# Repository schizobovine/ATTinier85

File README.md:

# ATTinier85
Smallish form factor ATTiny85 platform that doesn't bother with USB.

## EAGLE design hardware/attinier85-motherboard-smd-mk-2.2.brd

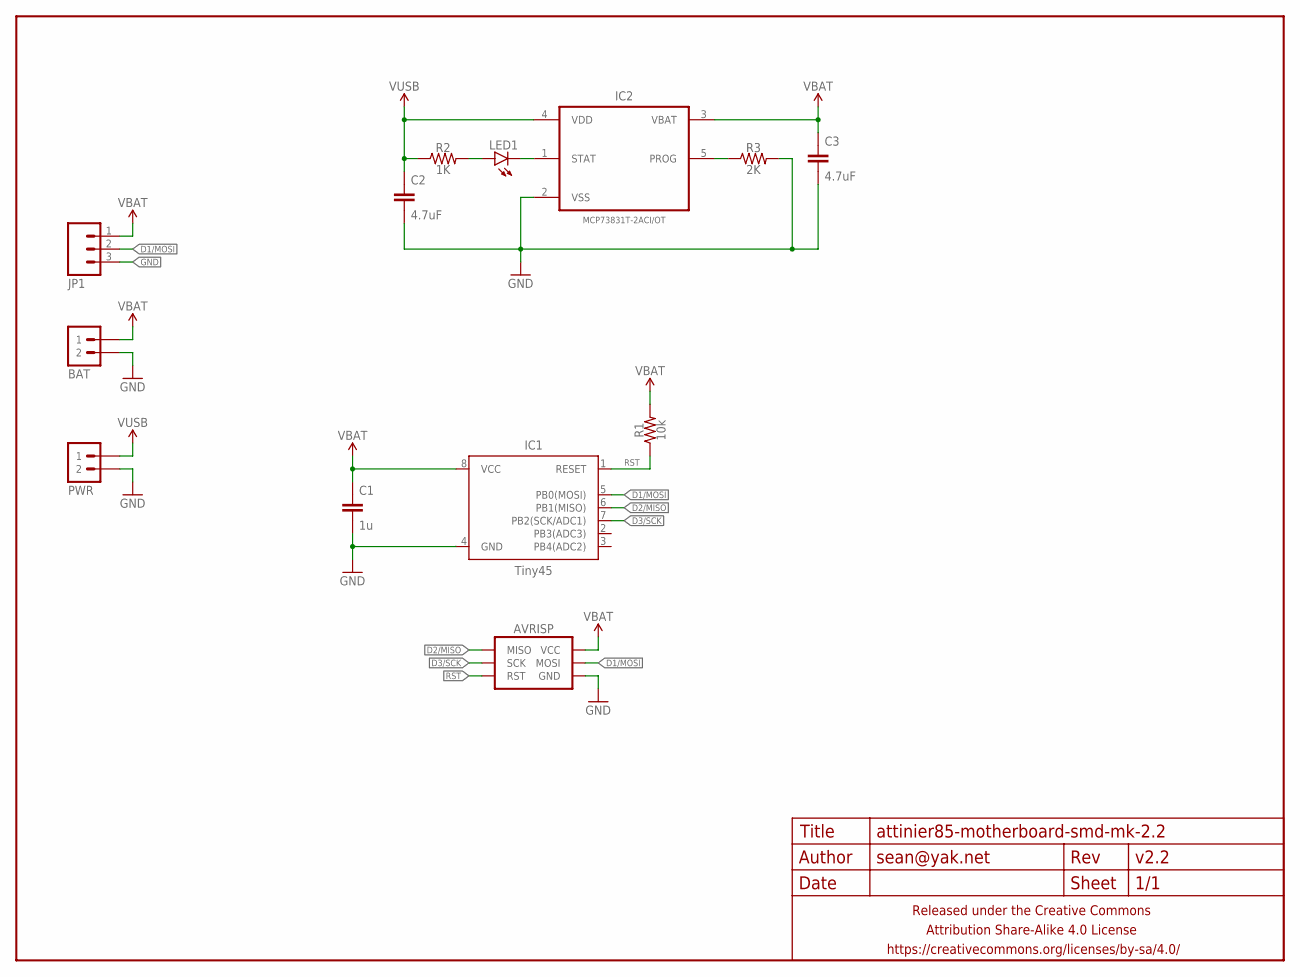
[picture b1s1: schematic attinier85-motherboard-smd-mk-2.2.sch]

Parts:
AVRISP: AVR_SPI_PRG_6SMD_TEST_POINTS; 2X3_SMD_TEST_POINTS
BAT: M02PTH-CENTERED; 1X02-CENTER
C1: 1u; C0603-TIGHTER
C2, C3: 4.7uF; C0603-TIGHTER
FRAME1: FRAME-LETTERNO_PACKAGE; DUMMY
IC1: Tiny45; SO08
IC2: MCP73831T-2ACI/OT; SOT95P280X145-5N
JP1: M03PTH-CENTERED; 1X03-CENTERED
LED1: LED0603-TIGHT; LED-0603-TIGHT
PWR: M02PTH-CENTERED; 1X02-CENTER
R1: 10k; R0603-TIGHTER
R2: 1K; R0603-TIGHTER
R3: 2K; R0603-TIGHTER

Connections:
D1/MOSI: AVRISP.4 (MOSI), IC1.5 (PB0(MOSI)), JP1.2
D2/MISO: AVRISP.1 (MISO), IC1.6 (PB1(MISO))
D3/SCK: AVRISP.3 (SCK), IC1.7 (PB2(SCK/ADC1))
GND: AVRISP.6 (GND), BAT.2, C1.2, C2.2, C3.2, IC1.4 (GND), IC2.2 (VSS), JP1.3, PWR.2, R3.2
unnamed: IC2.1 (STAT), LED1.C
unnamed: LED1.A, R2.2
unnamed: IC2.5 (PROG), R3.1
RST: AVRISP.5 (RST), IC1.1 (RESET), R1.1
VBAT: AVRISP.2 (VCC), BAT.1, C1.1, C3.1, IC1.8 (VCC), IC2.3 (VBAT), JP1.1, R1.2
VUSB: C2.1, IC2.4 (VDD), PWR.1, R2.1

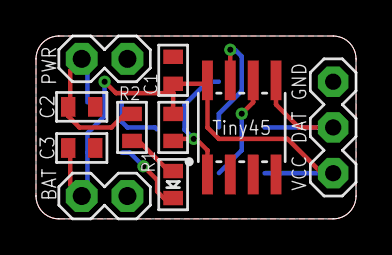
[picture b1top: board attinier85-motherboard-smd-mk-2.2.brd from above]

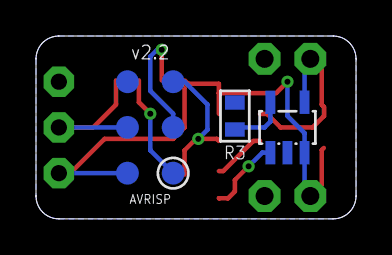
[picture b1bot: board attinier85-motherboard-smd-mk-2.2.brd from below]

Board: 2 copper layers, 17.8 x 10.2 mm, 14 parts (3 on the bottom side), 10 nets.

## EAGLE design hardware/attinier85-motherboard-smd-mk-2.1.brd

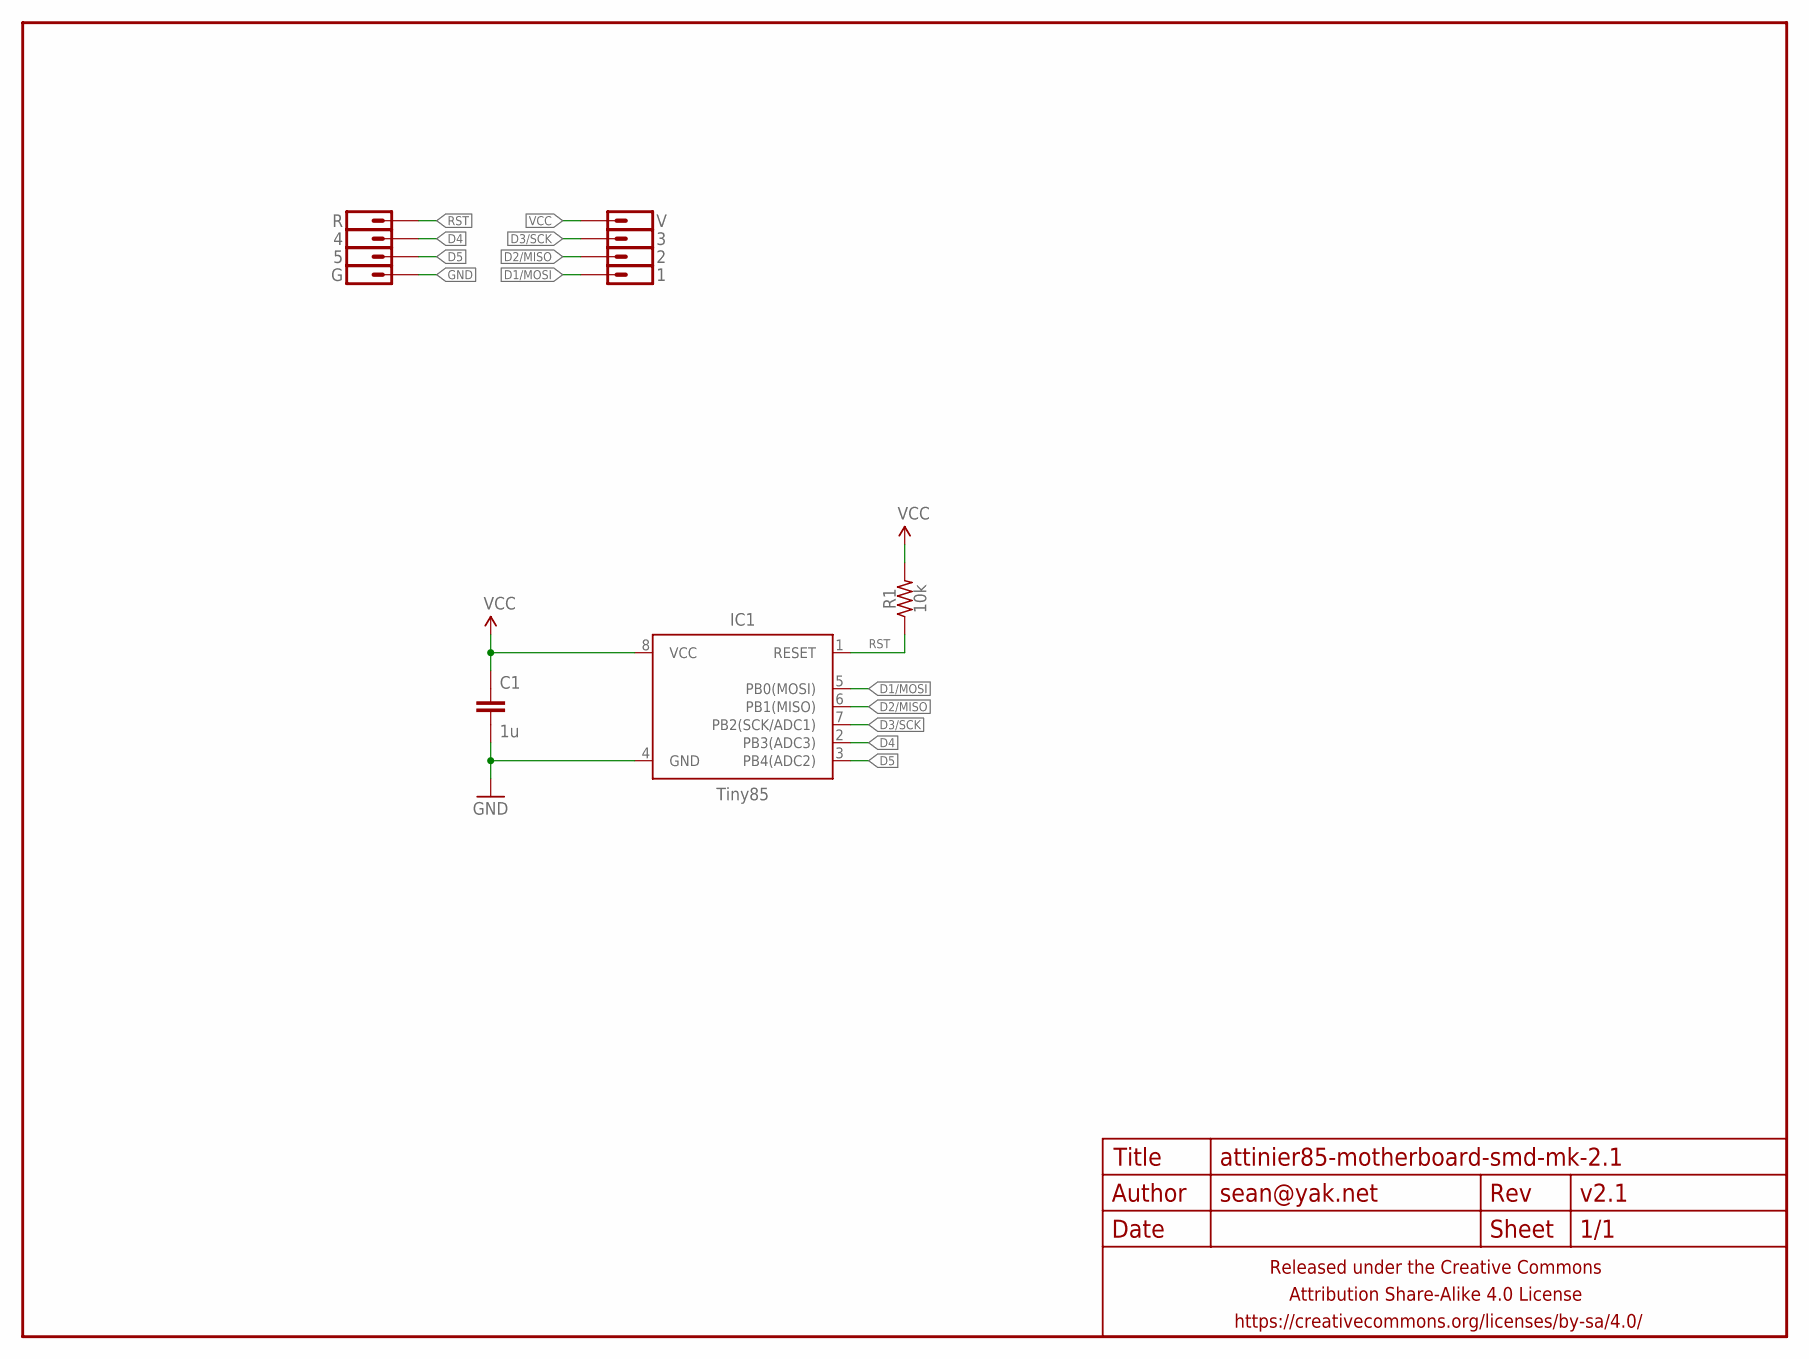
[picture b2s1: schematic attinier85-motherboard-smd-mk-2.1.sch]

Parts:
1, 2, 3, 4, 5: M01PTH-0.9MM; 1X01-0.9MM
C1: 1u; C0603-TIGHTER
FRAME1: FRAME-LETTERNO_PACKAGE; DUMMY
G: M01PTH-0.9MM; 1X01-0.9MM
IC1: Tiny85; SO08-EIAJ
R: M01PTH-0.9MM; 1X01-0.9MM
R1: 10k; R0603-TIGHTER
V: M01PTH-0.9MM; 1X01-0.9MM

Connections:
D1/MOSI: 1.1, IC1.5 (PB0(MOSI))
D2/MISO: 2.1, IC1.6 (PB1(MISO))
D3/SCK: 3.1, IC1.7 (PB2(SCK/ADC1))
D4: 4.1, IC1.2 (PB3(ADC3))
D5: 5.1, IC1.3 (PB4(ADC2))
GND: C1.2, G.1, IC1.4 (GND)
RST: IC1.1 (RESET), R.1, R1.1
VCC: C1.1, IC1.8 (VCC), R1.2, V.1

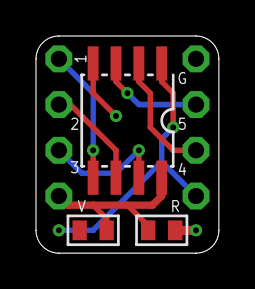
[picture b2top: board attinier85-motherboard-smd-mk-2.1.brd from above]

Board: 2 copper layers, 10.2 x 12.1 mm, 12 parts (0 on the bottom side), 8 nets.

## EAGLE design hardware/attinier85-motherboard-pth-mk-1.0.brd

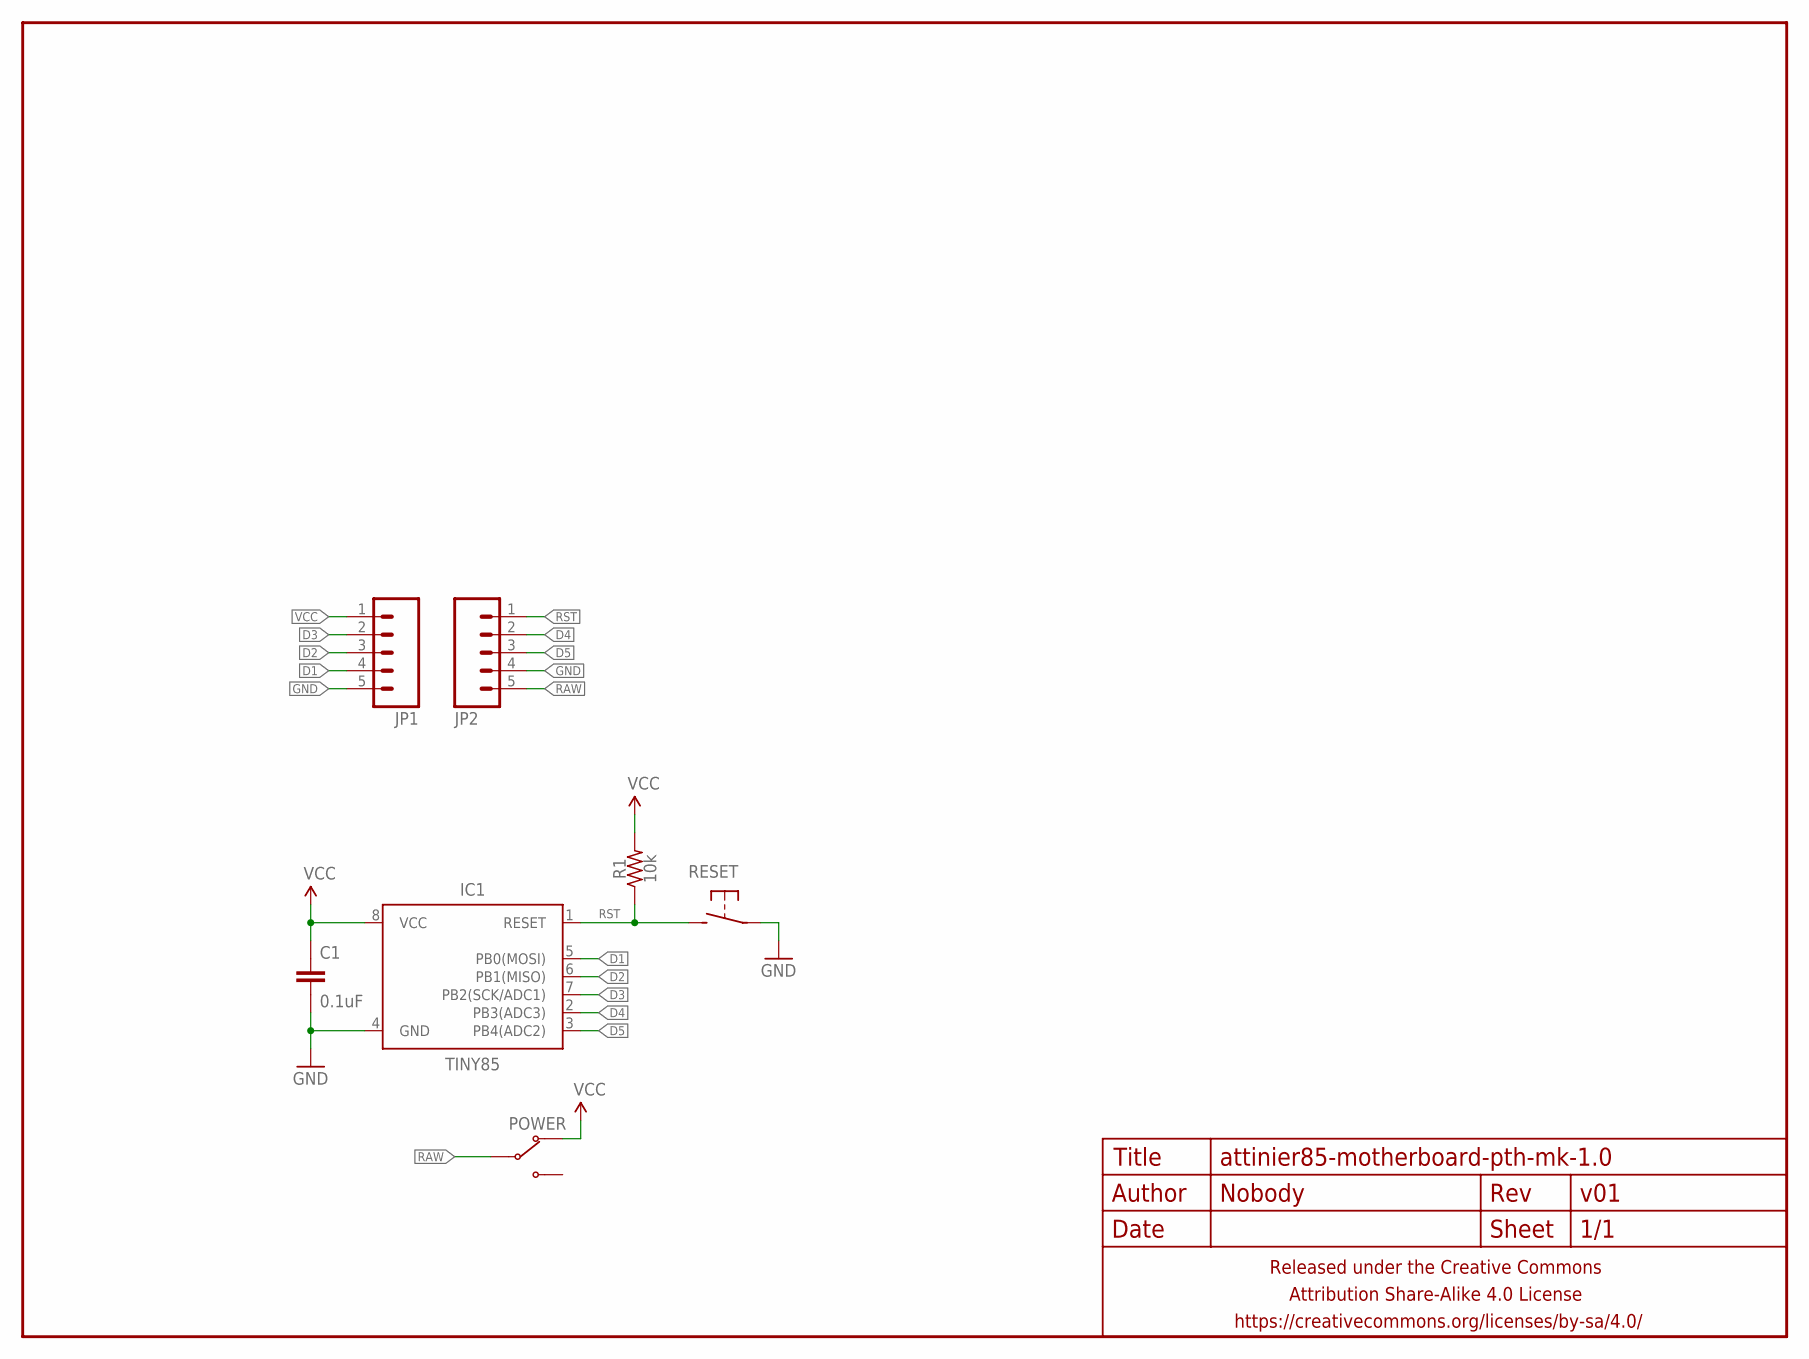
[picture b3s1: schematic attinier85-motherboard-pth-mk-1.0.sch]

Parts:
C1: 0.1uF; C025-024X044
FRAME1: FRAME-LETTERNO_PACKAGE; DUMMY
IC1: TINY85; DIP08
JP1, JP2: M05PTH; 1X05
POWER: SWITCH-SPDTPTH-RA-2.54MM; SPDT-RA-2.54MM
R1: 10k; RESISTOR-AXIAL-PTH-7.62MM
RESET: DTS-6MM; TACTILE-PTH-SIDE

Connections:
D1: IC1.5 (PB0(MOSI)), JP1.4
D2: IC1.6 (PB1(MISO)), JP1.3
D3: IC1.7 (PB2(SCK/ADC1)), JP1.2
D4: IC1.2 (PB3(ADC3)), JP2.2
D5: IC1.3 (PB4(ADC2)), JP2.3
GND: C1.2, IC1.4 (GND), JP1.5, JP2.4, RESET.1
RAW: JP2.5, POWER.2 (COM)
RST: IC1.1 (RESET), JP2.1, R1.P$1 (1), RESET.2
VCC: C1.1, IC1.8 (VCC), JP1.1, POWER.1 (NC), R1.P$2 (2)

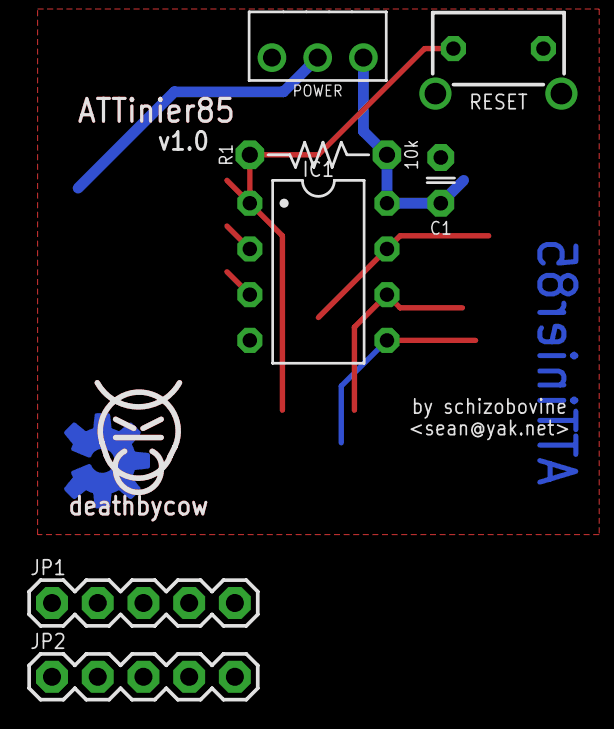
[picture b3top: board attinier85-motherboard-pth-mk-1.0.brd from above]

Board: 2 copper layers, 10 parts (1 on the bottom side), 9 nets.

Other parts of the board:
U$4: OSHWLOGO_TOP_0.2
U$5: COW_SMALL_METAL

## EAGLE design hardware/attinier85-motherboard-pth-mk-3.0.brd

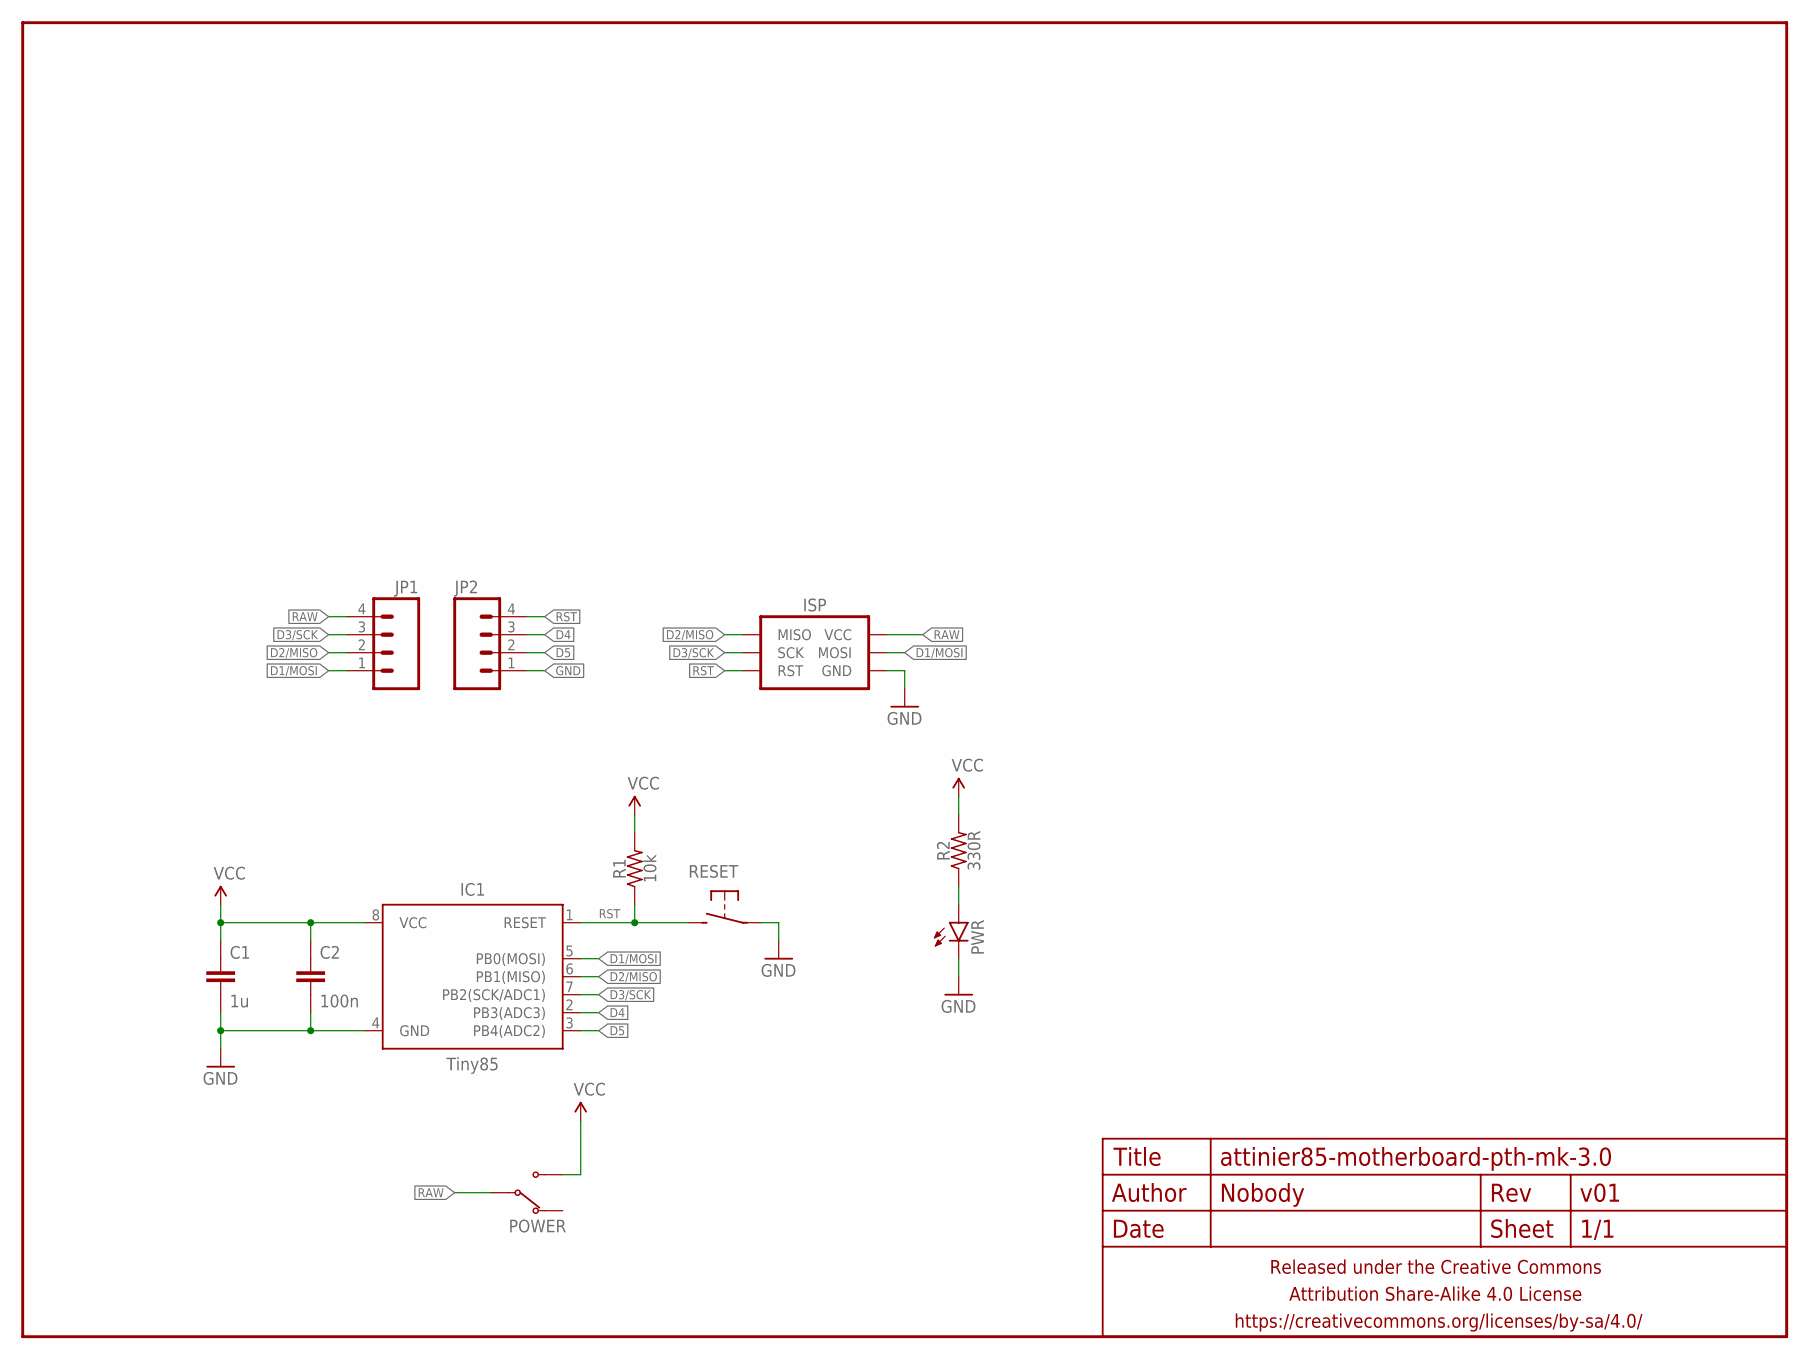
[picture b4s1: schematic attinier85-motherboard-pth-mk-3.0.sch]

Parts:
C1: 1u; C0603
C2: 100n; C0603
FRAME1: FRAME-LETTERNO_PACKAGE; DUMMY
IC1: Tiny85; SO08-EIAJ
ISP: AVR_SPI_PRG_62X3_SMD; 2X3_SMD
JP1, JP2: M04PTH; 1X04-PTH-VERT
POWER: SWITCH-SPDTSMD-RA; SWITCH-SPDT-SMD-RA
PWR: LED0603; LED-0603
R1: 10k; R0603
R2: 330R; R0603
RESET: DTS-6MM; B3U-1000P

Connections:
D1/MOSI: IC1.5 (PB0(MOSI)), ISP.4 (MOSI), JP1.1
D2/MISO: IC1.6 (PB1(MISO)), ISP.1 (MISO), JP1.2
D3/SCK: IC1.7 (PB2(SCK/ADC1)), ISP.3 (SCK), JP1.3
D4: IC1.2 (PB3(ADC3)), JP2.3
D5: IC1.3 (PB4(ADC2)), JP2.2
GND: C1.2, C2.2, IC1.4 (GND), ISP.6 (GND), JP2.1, PWR.C, RESET.0 (1)
unnamed: PWR.A, R2.1
RAW: ISP.2 (VCC), JP1.4, POWER.2 (COM)
RST: IC1.1 (RESET), ISP.5 (RST), JP2.4, R1.1, RESET.1 (2)
VCC: C1.1, C2.1, IC1.8 (VCC), POWER.1 (NO), R1.2, R2.2

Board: 2 copper layers, 12 parts (6 on the bottom side), 10 nets, no tracks yet.

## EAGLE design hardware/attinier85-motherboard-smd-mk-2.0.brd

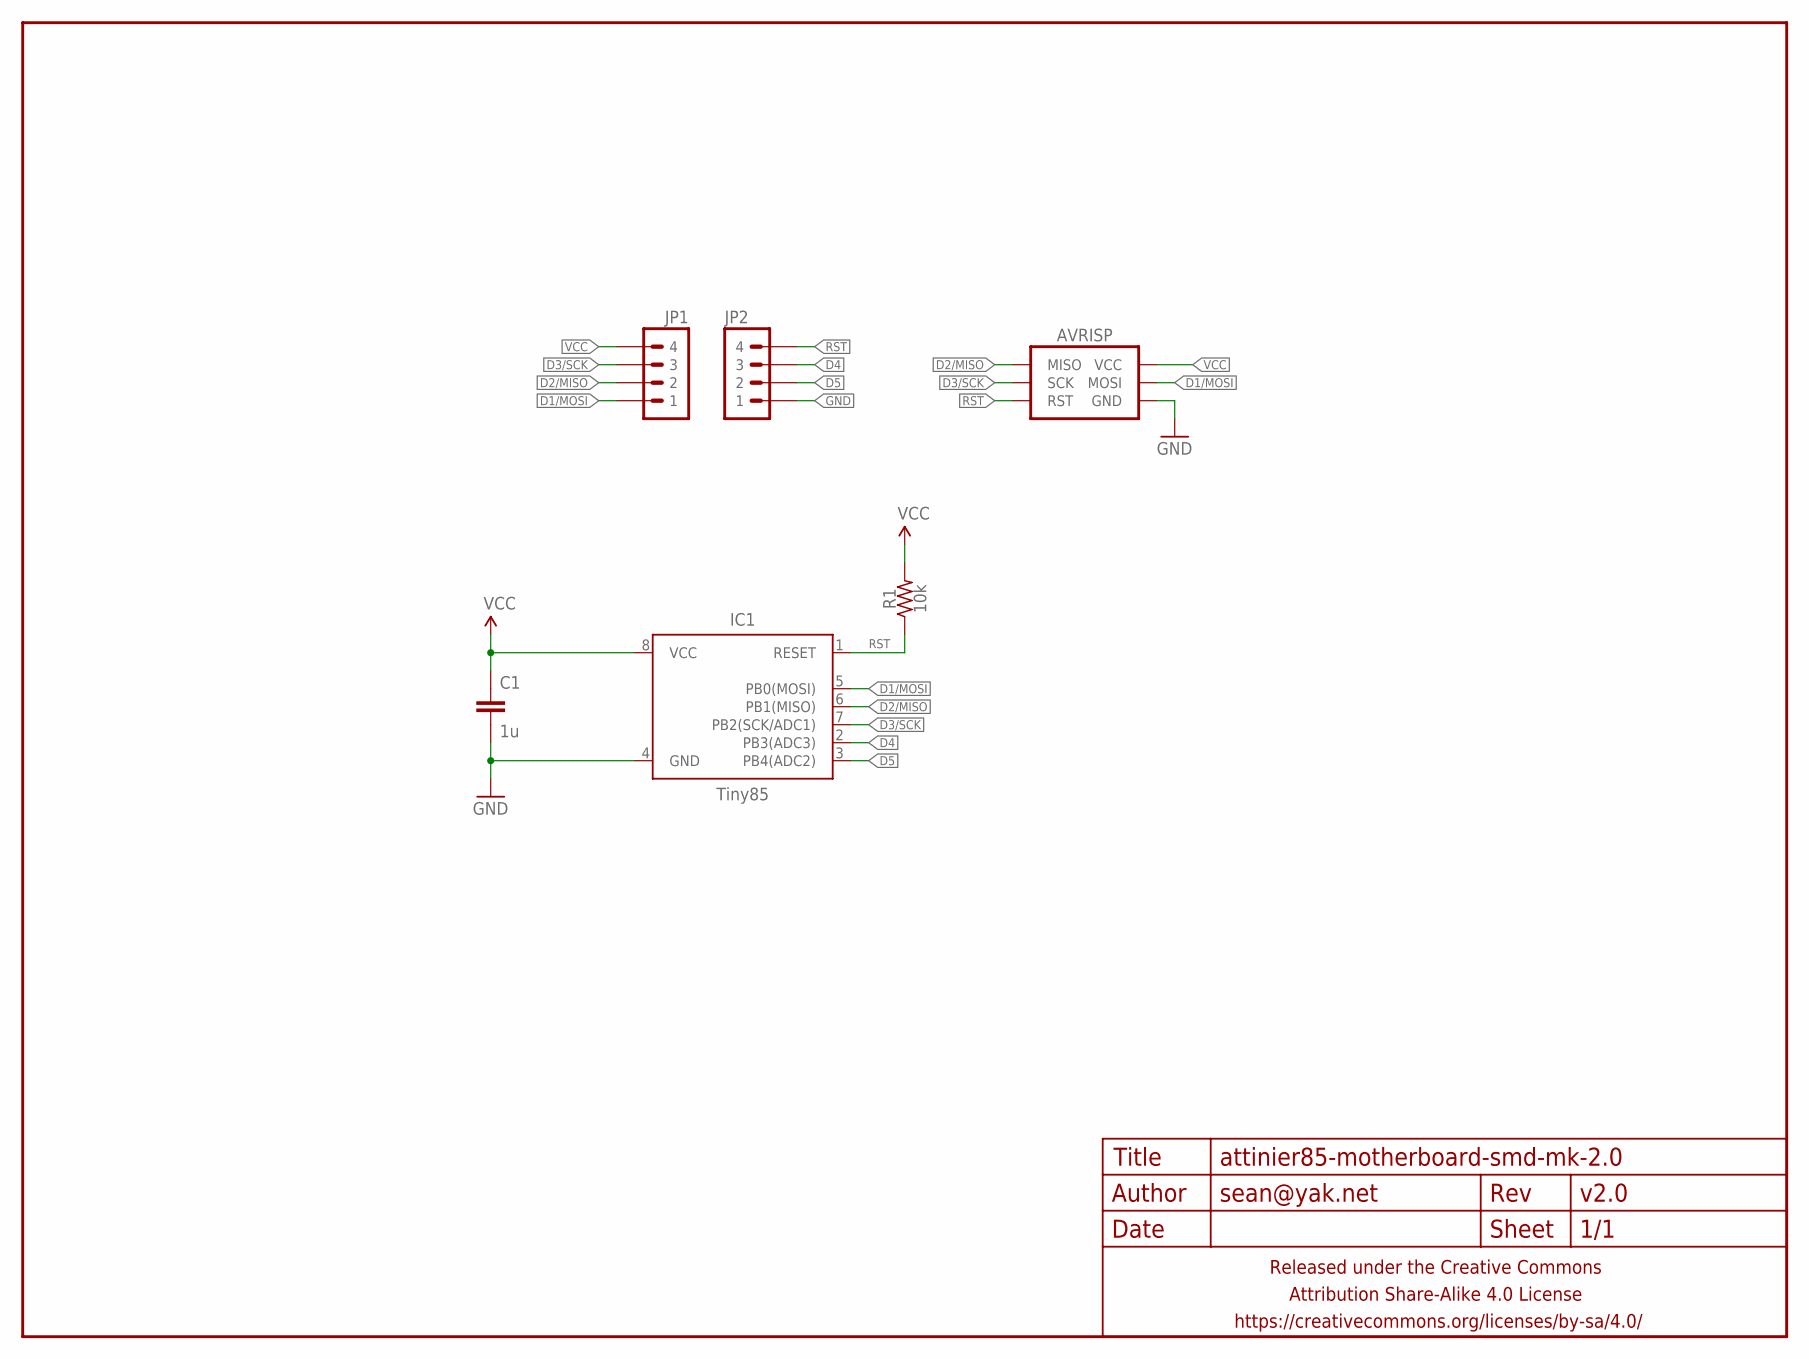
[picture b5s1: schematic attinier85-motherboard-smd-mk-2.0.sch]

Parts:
AVRISP: AVR_SPI_PRG_6SMD_TEST_POINTS; 2X3_SMD_TEST_POINTS
C1: 1u; C0603-TIGHTER
FRAME1: FRAME-LETTERNO_PACKAGE; DUMMY
IC1: Tiny85; SO08-EIAJ
JP1, JP2: M04PTH; 1X04-PTH-VERT
R1: 10k; R0603-TIGHTER

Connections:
D1/MOSI: AVRISP.4 (MOSI), IC1.5 (PB0(MOSI)), JP1.1
D2/MISO: AVRISP.1 (MISO), IC1.6 (PB1(MISO)), JP1.2
D3/SCK: AVRISP.3 (SCK), IC1.7 (PB2(SCK/ADC1)), JP1.3
D4: IC1.2 (PB3(ADC3)), JP2.3
D5: IC1.3 (PB4(ADC2)), JP2.2
GND: AVRISP.6 (GND), C1.2, IC1.4 (GND), JP2.1
RST: AVRISP.5 (RST), IC1.1 (RESET), JP2.4, R1.1
VCC: AVRISP.2 (VCC), C1.1, IC1.8 (VCC), JP1.4, R1.2

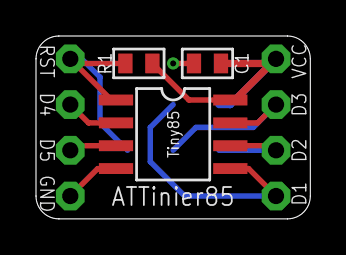
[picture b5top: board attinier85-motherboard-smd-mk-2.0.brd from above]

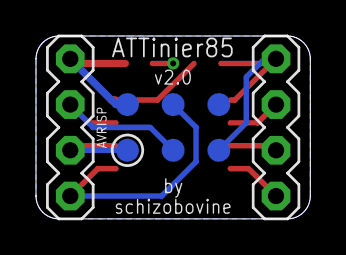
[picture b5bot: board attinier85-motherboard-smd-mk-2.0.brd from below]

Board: 2 copper layers, 15.2 x 10.2 mm, 7 parts (3 on the bottom side), 8 nets.

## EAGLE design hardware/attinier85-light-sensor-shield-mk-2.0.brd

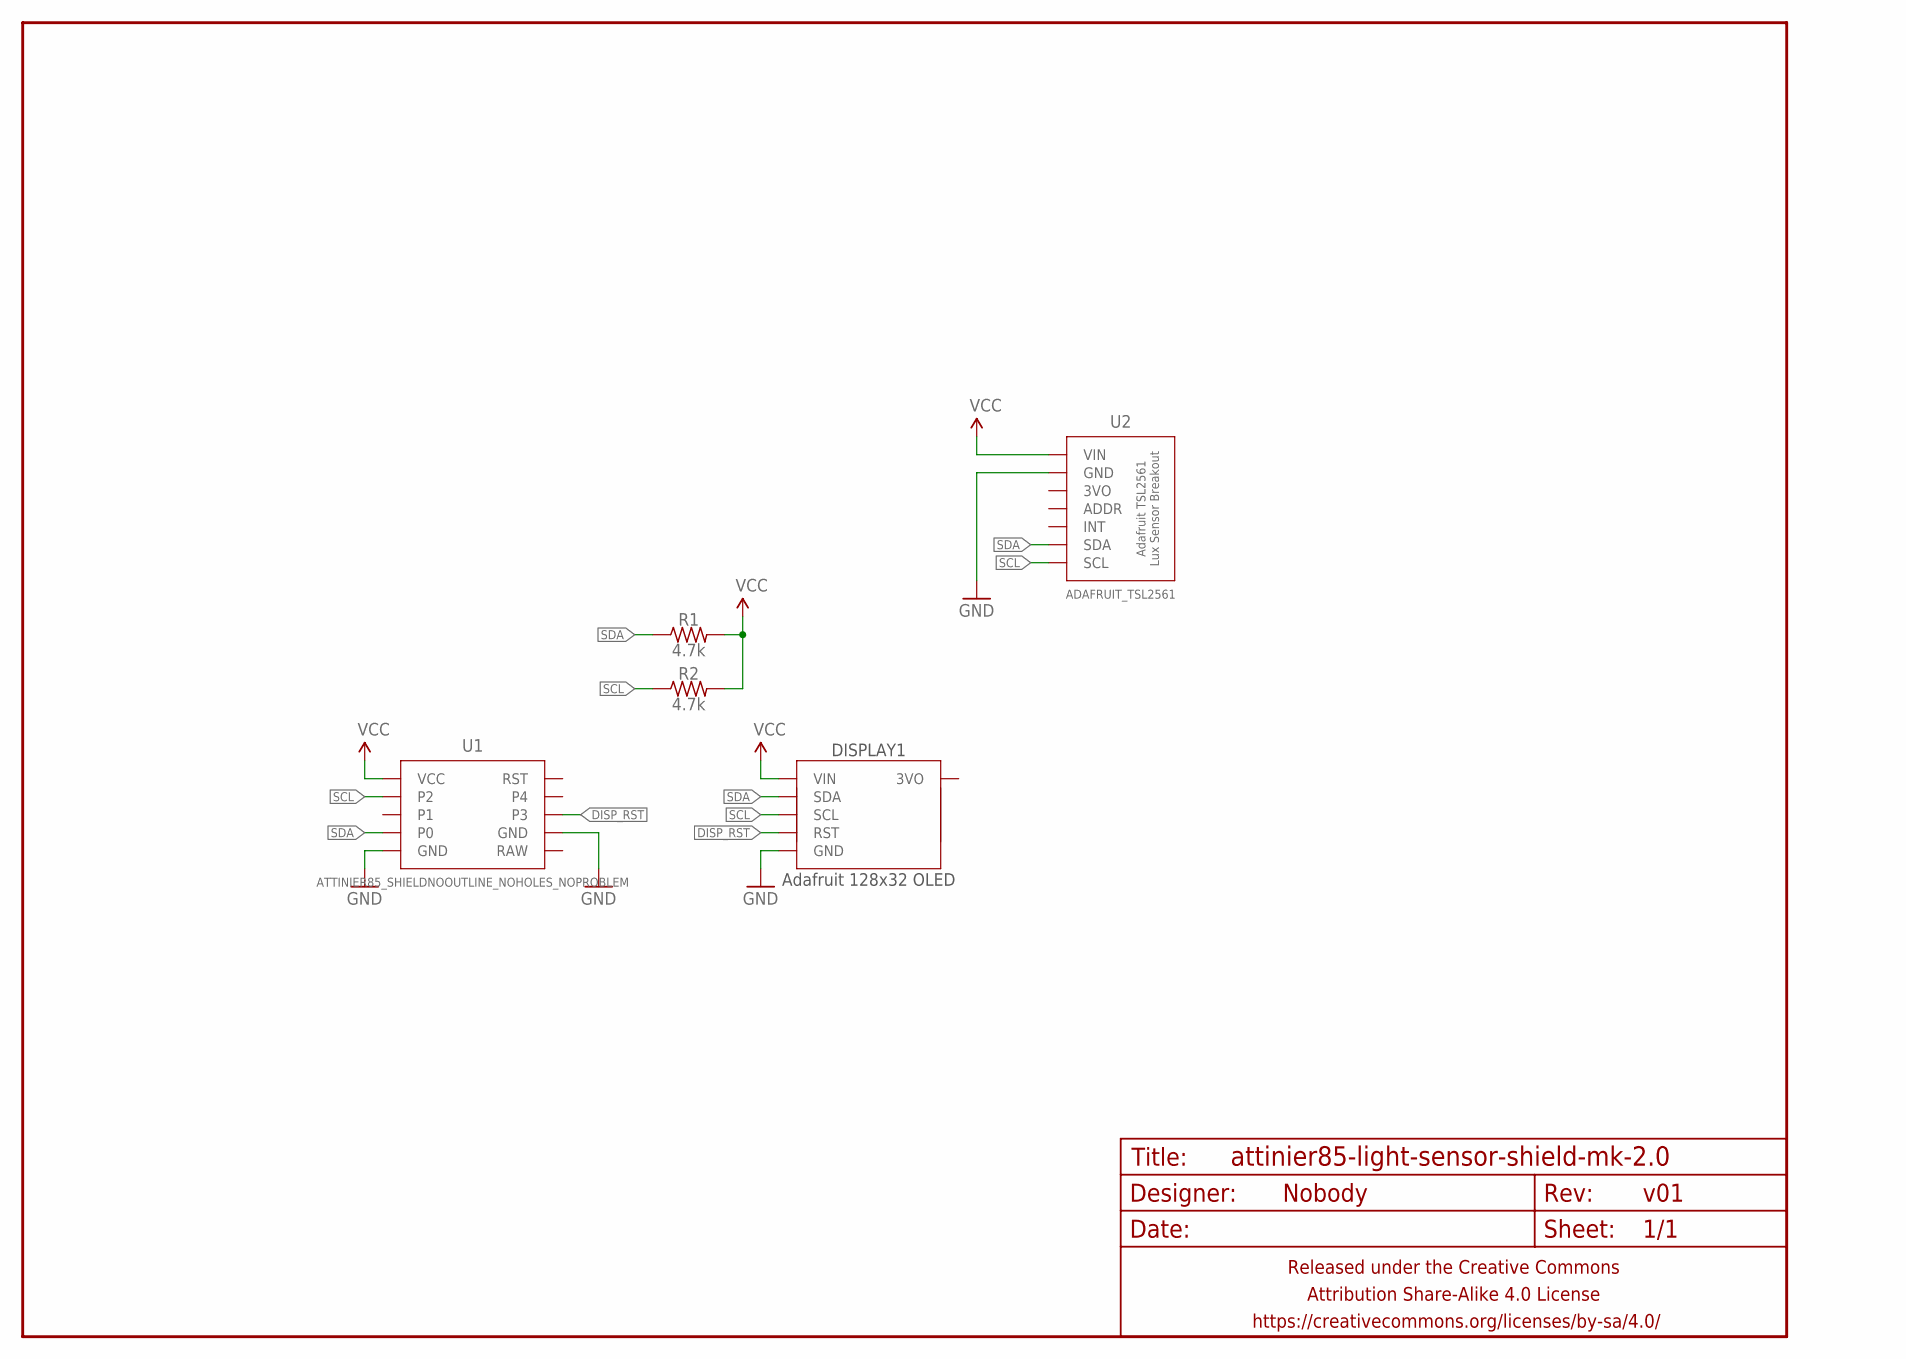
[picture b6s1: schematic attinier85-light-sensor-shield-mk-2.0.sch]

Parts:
DISPLAY1: Adafruit 128x32 OLED; ADAFRUIT_128X32_OLED_I2C_CLOSER_NOTITLE
FRAME1: FRAME-LETTERNO_PACKAGE; DUMMY
R1, R2: 4.7k; RESISTOR-AXIAL-PTH-7.62MM
U1: ATTINIER85_SHIELDNOOUTLINE_NOHOLES_NOPROBLEM; ATTINIER_SHIELD_NOOUTLINE_NOHOLES
U2: ADAFRUIT_TSL2561

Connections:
DISP_RST: DISPLAY1.RST, U1.3
GND: DISPLAY1.GND, U1.GND@1 (GND), U1.GND@2 (GND), U2.GND
SCL: DISPLAY1.SCL, R2.P$1 (1), U1.2, U2.SCL
SDA: DISPLAY1.SDA, R1.P$1 (1), U1.0, U2.SDA
VCC: DISPLAY1.VIN, R1.P$2 (2), R2.P$2 (2), U1.VCC, U2.VIN

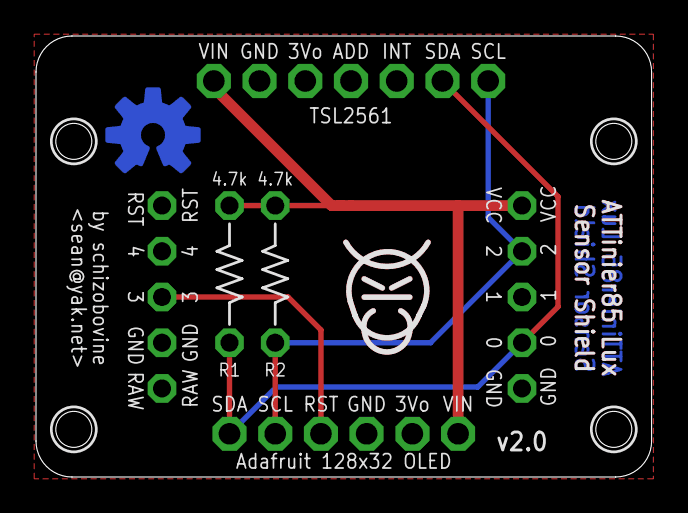
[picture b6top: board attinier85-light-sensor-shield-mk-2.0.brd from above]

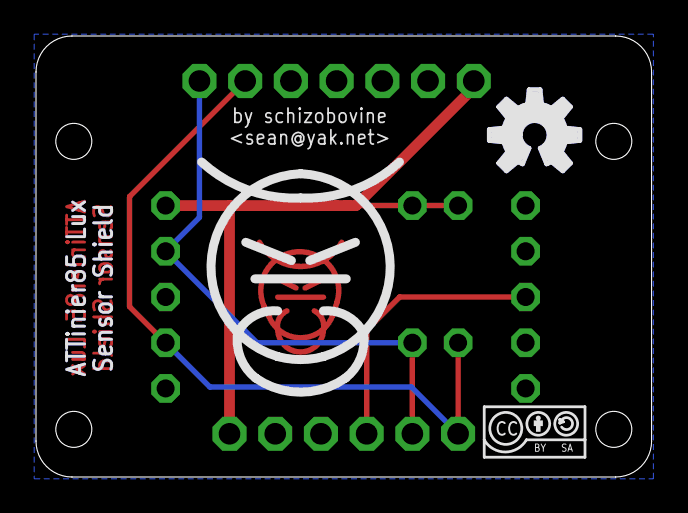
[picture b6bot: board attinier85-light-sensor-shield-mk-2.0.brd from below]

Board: 2 copper layers, 34.2 x 24.5 mm, 10 parts (3 on the bottom side), 5 nets.

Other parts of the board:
U$1: COW
U$2: CC-BY-SA-4.0-NO-URL
U$3: OSHWLOGO_TOP_0.2
U$5: COW_SMALL_METAL_NOTEXT

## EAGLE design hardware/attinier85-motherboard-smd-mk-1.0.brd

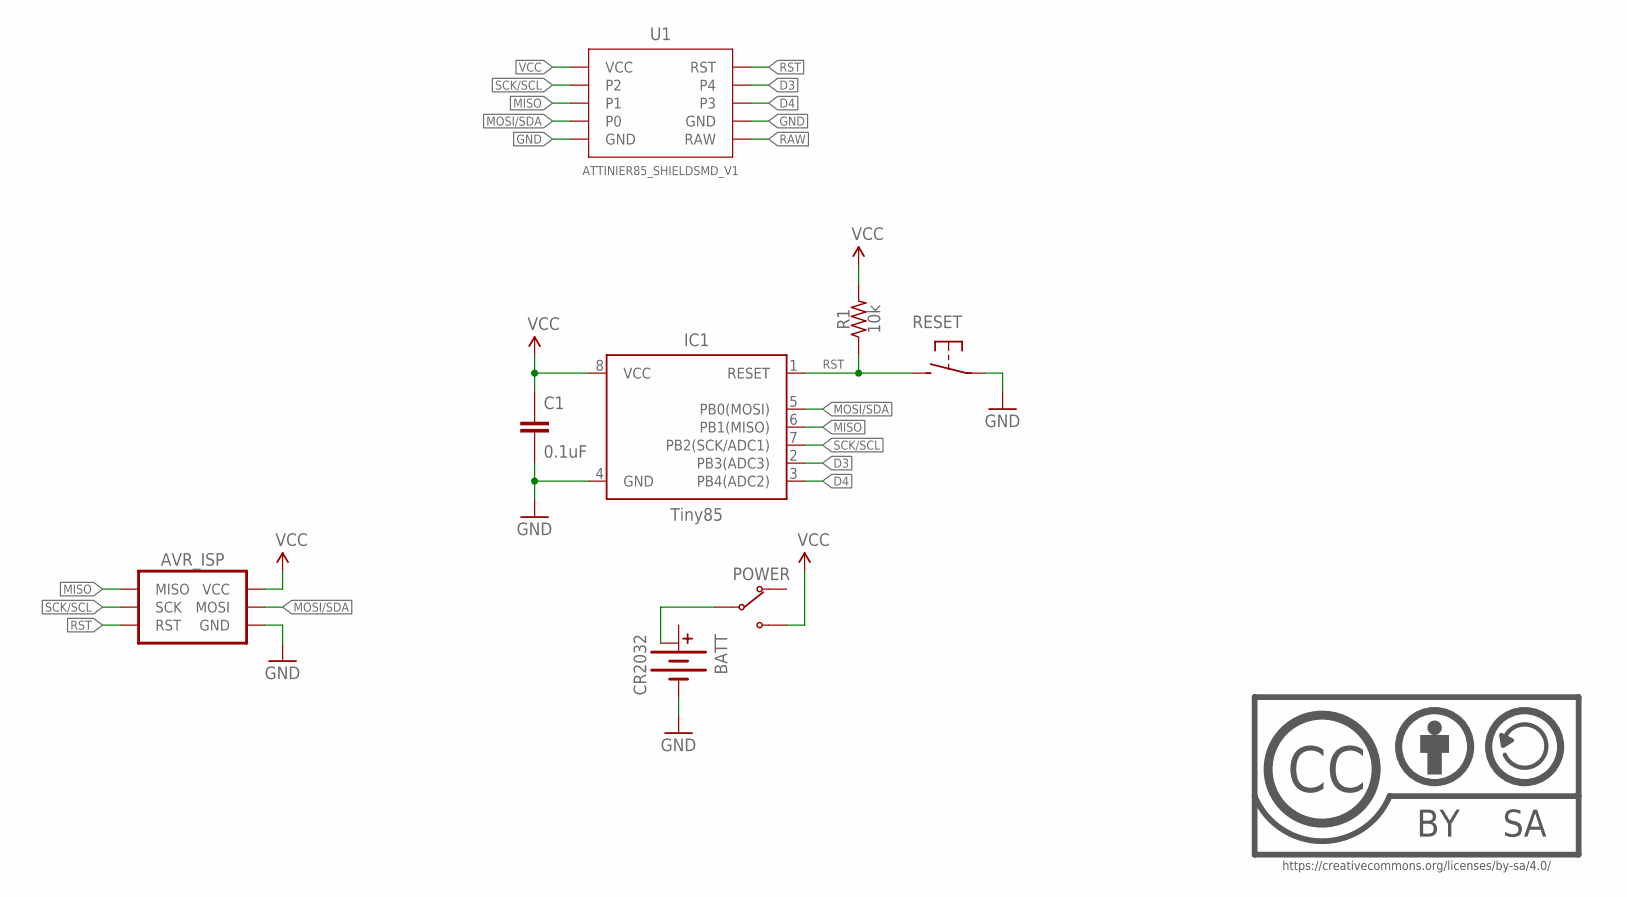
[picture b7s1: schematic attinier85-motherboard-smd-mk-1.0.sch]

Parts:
AVR_ISP: AVR_SPI_PRG_62X3_SMD; 2X3_SMD
BATT: CR2032; BATTCON_20MM_MINE
C1: 0.1uF; C0805
IC1: Tiny85; SO08-EIAJ
POWER: SWITCH-SPDTPTH-RA-2.54MM; SPDT-RA-2.54MM
R1: 10k; R0805
RESET: DTS-6MM; TACTILE-PTH-SIDE
U1: ATTINIER85_SHIELDSMD_V1; ATTINIER85_SHIELD_SMD
U$1: CC-BY-SA-4.0NO-URL; CC-BY-SA-4.0-NO-URL

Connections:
D3: IC1.2 (PB3(ADC3)), U1.4
D4: IC1.3 (PB4(ADC2)), U1.3
GND: AVR_ISP.6 (GND), BATT.BOTTOM (-), C1.2, IC1.4 (GND), RESET.1, U1.GND@1 (GND), U1.GND@2 (GND)
MISO: AVR_ISP.1 (MISO), IC1.6 (PB1(MISO)), U1.1
MOSI/SDA: AVR_ISP.4 (MOSI), IC1.5 (PB0(MOSI)), U1.0
unnamed: BATT.TOP@2 (+1), POWER.2 (COM)
RAW: U1.RAW
RST: AVR_ISP.5 (RST), IC1.1 (RESET), R1.1, RESET.2, U1.RST
SCK/SCL: AVR_ISP.3 (SCK), IC1.7 (PB2(SCK/ADC1)), U1.2
VCC: AVR_ISP.2 (VCC), C1.1, IC1.8 (VCC), POWER.3 (NO), R1.2, U1.VCC

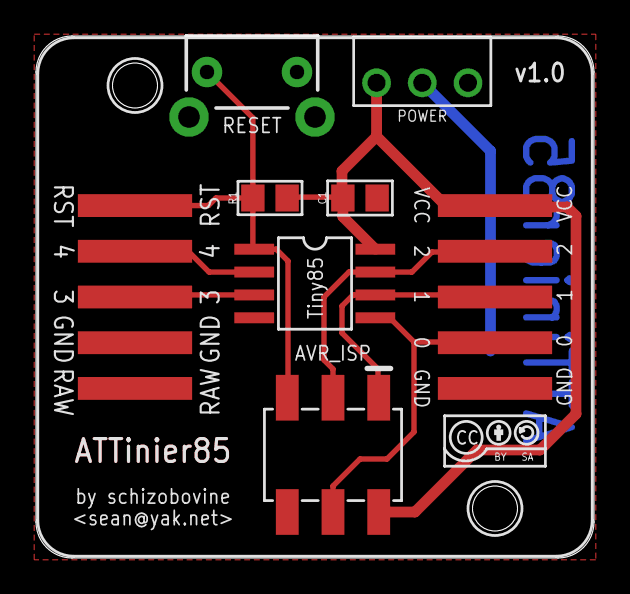
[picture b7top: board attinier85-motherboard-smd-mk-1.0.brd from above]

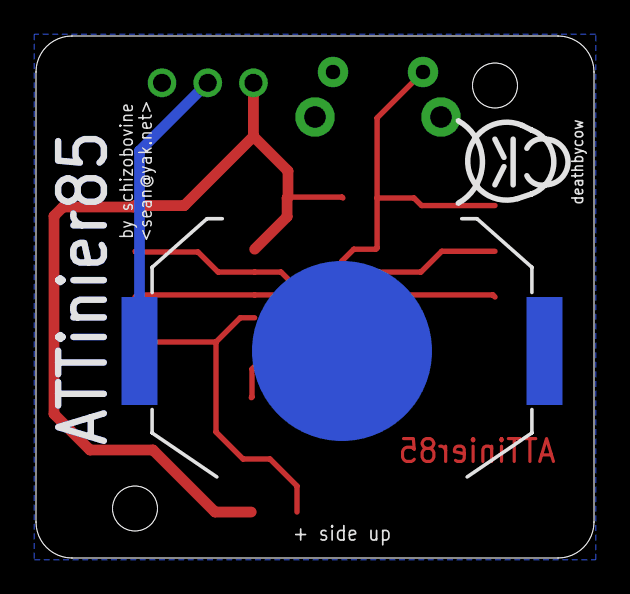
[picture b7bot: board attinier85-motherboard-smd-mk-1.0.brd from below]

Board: 2 copper layers, 31.0 x 29.0 mm, 10 parts (2 on the bottom side), 9 nets.

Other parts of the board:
U$3: COW_SMALL

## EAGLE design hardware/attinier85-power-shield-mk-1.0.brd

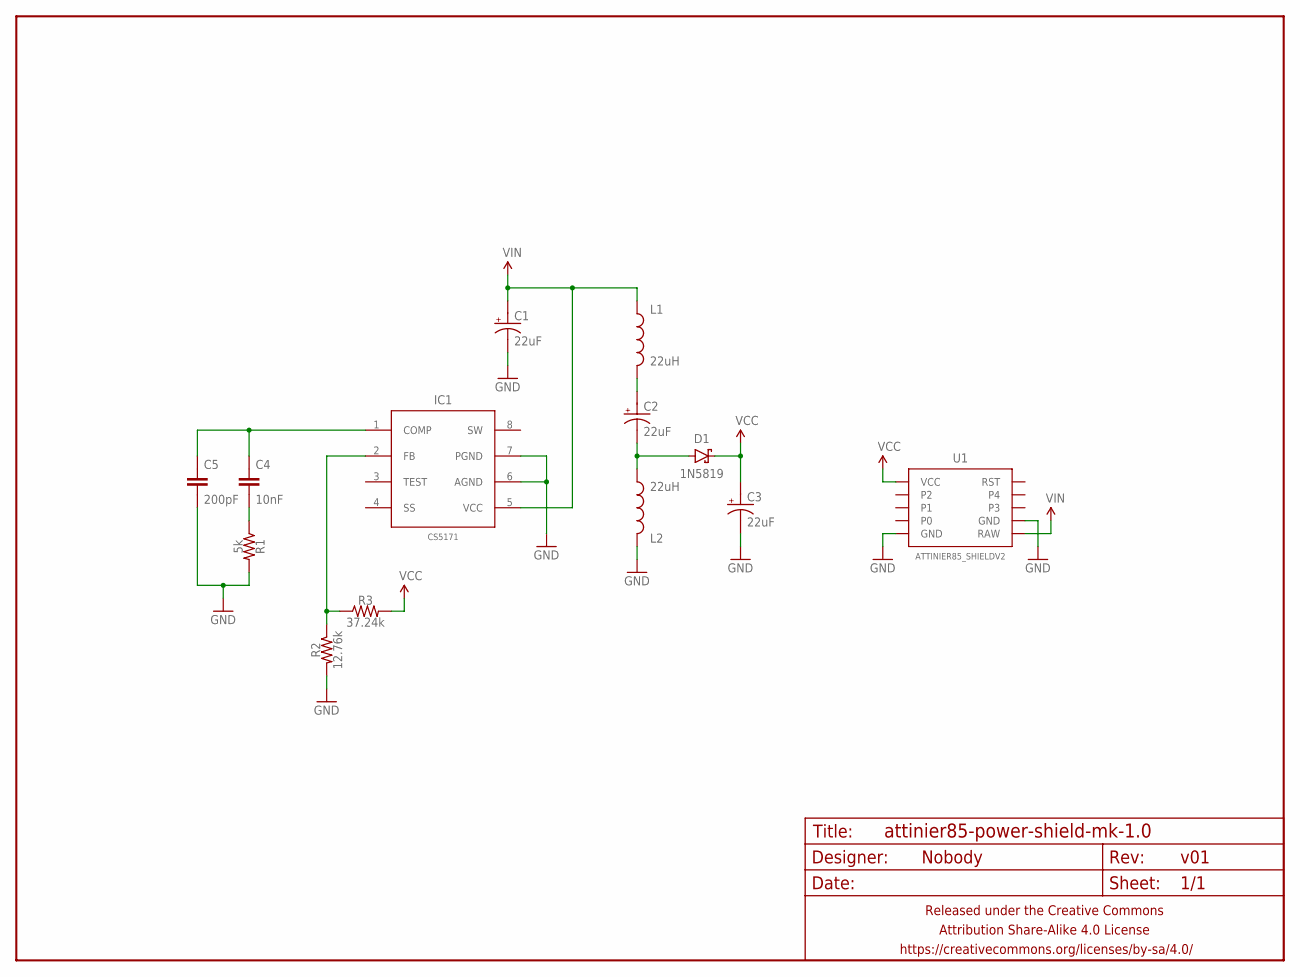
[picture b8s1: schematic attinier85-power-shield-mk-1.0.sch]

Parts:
C1, C2, C3: 22uF; E2,5-6
C4: 10nF; C025-024X044
C5: 200pF; C025-024X044
D1: 1N5819; DIODE-10.16MM
FRAME1: FRAME-LETTERNO_PACKAGE; DUMMY
IC1: CS5171; SO08
L1, L2: 22uH; INDUCTOR-AXIAL-PTH-10.16MM
R1: 5k; RESISTOR-AXIAL-PTH-6.35MM
R2: 12.76k; RESISTOR-AXIAL-PTH-6.35MM
R3: 37.24k; RESISTOR-AXIAL-PTH-6.35MM
U1: ATTINIER85_SHIELDV2; ATTINIER85_SHIELD_V2

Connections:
GND: C1.-, C3.-, C5.2, IC1.6 (AGND), IC1.7 (PGND), L2.P$1 (1), R1.P$2 (2), R2.P$2 (2), U1.GND@1 (GND), U1.GND@2 (GND)
unnamed: C4.2, R1.P$1 (1)
unnamed: C4.1, C5.1, IC1.1 (COMP)
unnamed: IC1.2 (FB), R2.P$1 (1), R3.P$1 (1)
unnamed: C2.+, L1.P$2 (2)
unnamed: C2.-, D1.A, L2.P$2 (2)
VCC: C3.+, D1.C, R3.P$2 (2), U1.VCC
VIN: C1.+, IC1.5 (VCC), L1.P$1 (1), U1.RAW

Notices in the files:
parts and their libraries:
A_butts: Released under the Creative Commons Attribution Share-Alike 4.0 License
A_butts: https://creativecommons.org/licenses/by-sa/4.0
A_butts: Released under the Creative Commons
A_butts: creativecommons.org/licenses/by-sa/4.0
